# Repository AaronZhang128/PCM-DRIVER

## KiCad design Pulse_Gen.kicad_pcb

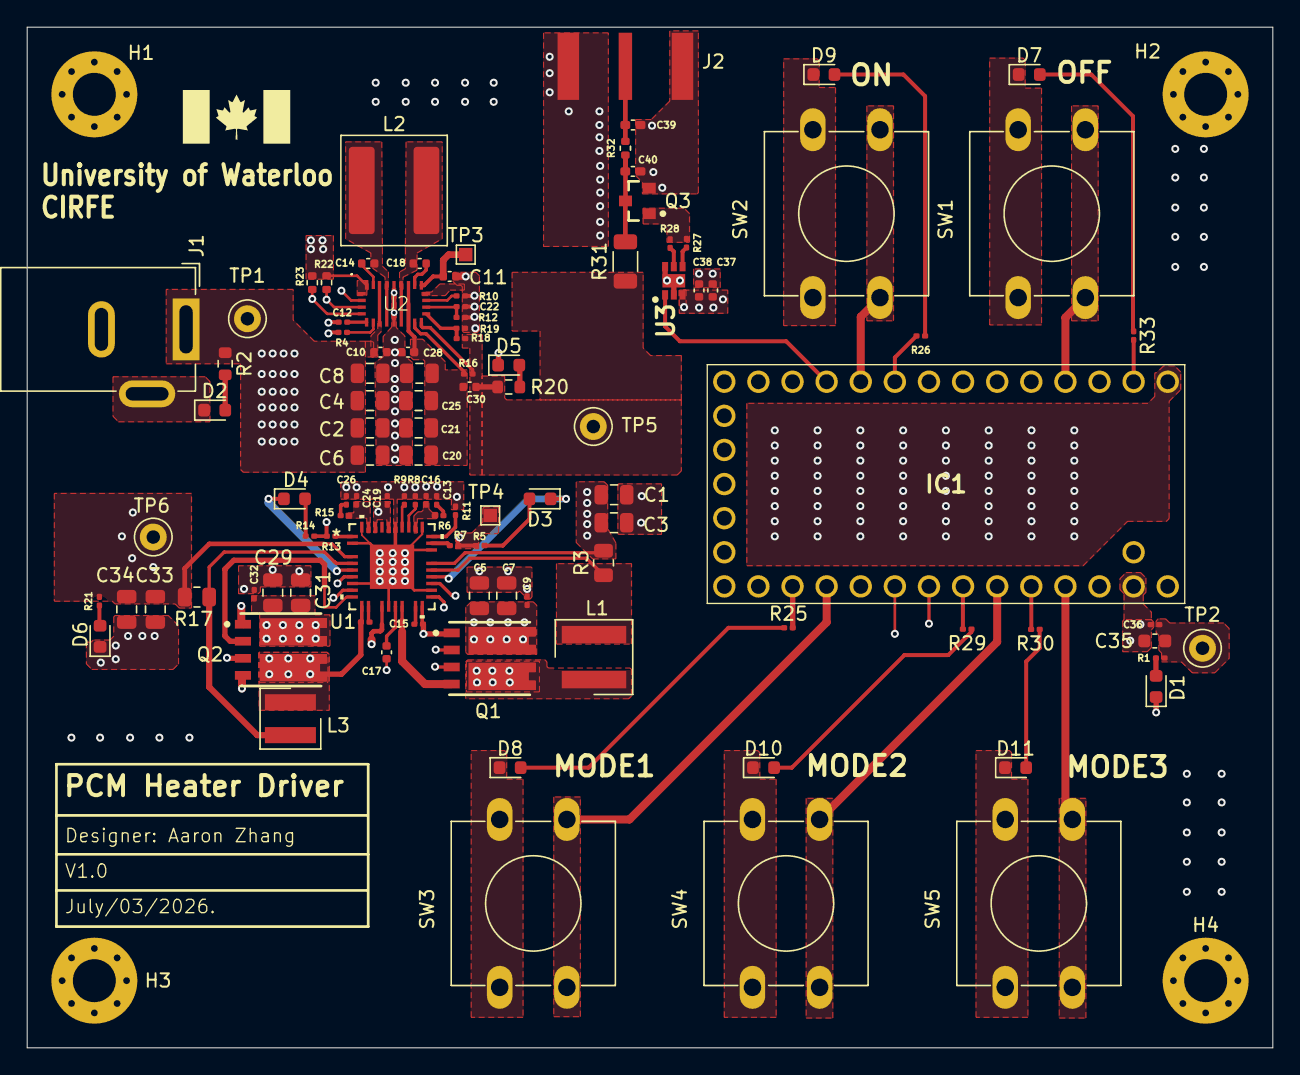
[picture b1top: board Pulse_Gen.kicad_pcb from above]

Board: 4 copper layers, 92.8 x 76.0 mm, 110 parts (0 on the bottom side), 68 nets.

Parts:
C1, C2, C3, C4, C5, C6, C7, C8, C20, C21, C25, C27, C29, C31, C33, C34: 22uF; C_0805_2012Metric
C9, C32: 10nF; C_0201_0603Metric
C10, C14, C18, C28, C30, C37: 0.1uF; C_0402_1005Metric
C11, C17: 4.7uF; C_0402_1005Metric
C12: 0.01uF; C_0201_0603Metric
C13: 4.7nF; C_0201_0603Metric
C15, C23, C36: 0.1uF; C_0201_0603Metric
C16: 82pF; C_0201_0603Metric
C19: 1uF; C_0201_0603Metric
C22: 12nF; C_0201_0603Metric
C24: 120pF; C_0201_0603Metric
C26: 8.2nF; C_0201_0603Metric
C35: 10uF; C_0603_1608Metric
C38: 1uF; C_0402_1005Metric
C39, C40: DNI; C_0402_1005Metric_Pad0.74x0.62mm_HandSolder
D1, D9: LED_G; LED_0603_1608Metric
D2, D8: LED_Y; LED_0603_1608Metric
D3, D4, D5, D7, D10: LED_R; LED_0603_1608Metric
D6, D11: LED_B; LED_0603_1608Metric
H1, H2, H3, H4: MountingHole_Pad; MountingHole_3.2mm_M3_Pad_Via
IC1: TEENSY_4.0; TEENSY40
J1: Barrel_Jack_Switch; BarrelJack_GCT_DCJ200-10-A_Horizontal
J2: 2081880-1; TE_2081880-1
L1: 4.7uH; L_Wurth_WE-XHMI-5030
L2: 4.7uH; L_Coilcraft_XAL7070-XXX
L3: 3.3uH; L_Wurth_WE-XHMI-4040
Q1, Q2: IPG20N04S4L-08A; INF-PG-TDSON-8-10
Q3: IRLML0040; SOT95P237X112-3N-2-V
R1, R5, R14, R29, R33: 604R; R_0201_0603Metric
R2, R20: 4k53; R_0603_1608Metric
R3: 8mR; R_0805_2012Metric
R4: 49K9; R_0201_0603Metric
R6: 8.45K; R_0201_0603Metric
R7: 24K9; R_0201_0603Metric
R8: 20K; R_0201_0603Metric
R9: 52.3K; R_0201_0603Metric
R10: DNI; R_0201_0603Metric
R11: 10K; R_0201_0603Metric
R12: 18k; R_0201_0603Metric
R13: 7.5K; R_0201_0603Metric
R15: 6.04K; R_0201_0603Metric
R16: 10m; R_0201_0603Metric
R17: 9mR; R_0805_2012Metric
R18: 100k; R_0201_0603Metric
R19: 5k76; R_0201_0603Metric
R21: 300R; R_0201_0603Metric
R22, R23: 4.7K; R_0402_1005Metric
R25: 510R; R_0201_0603Metric
R26: 570R; R_0201_0603Metric
R27, R28: 2R; R_0201_0603Metric
R30: 340R; R_0201_0603Metric
R31: 50R; R_1206_3216Metric
R32: 0R; R_0402_1005Metric
SW1, SW2, SW3, SW4, SW5: SW_Push; SW_PUSH-12mm
TP1: 24VIN; TestPoint_Keystone_5000-5004_Miniature
TP2, TP5, TP6: TestPoint; TestPoint_Keystone_5000-5004_Miniature
TP3, TP4: TestPoint; TestPoint_Pad_1.0x1.0mm
U1: VQFN36_6P1X6P1_TEX
U2: TPS55287_CORRECT
U3: SON65P200X200X80-7N

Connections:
+3.3V: C33.1, C34.1, R17.2, R21.1, R22.2, R23.2, TP6.1 (1_1), U1.3 (VOUT2), U2.1 (EN/UVLO), U2.21 (EXTVCC)
+5V: C1.1, C3.1, C35.1, C36.1, C37.2, C38.2, IC1.33 (VIN_(3.6_TO_5.5_VOLTS)), R1.1, R3.2, TP2.1 (1_1), U1.23 (BIAS1/VOUT1), U3.3 (VDD)
/FET/IRLML_G: Q3.1 (GATE), R27.1, R28.1
/FET/OUTH: R27.2, U3.4 (OUTH)
/FET/OUTL: R28.2, U3.5 (OUTL)
/MCU/D7: D8.2 (A), R25.1
/MCU/D8: D10.2 (A), R29.1
/MCU/D9: D11.2 (A), R30.1
/MCU/D10: D7.2 (A), R33.1
/MCU/D11: D9.2 (A), R26.1
/MCU/MCU_PIN0: IC1.2 (0), R33.2
/MCU/MCU_PIN2: IC1.4 (2), SW1.2
/MCU/MCU_PIN7: IC1.9 (7), R26.2
/MCU/MCU_PIN8: IC1.10 (8), SW2.2
/MCU/MCU_PIN15: IC1.22 (15), R25.2
/MCU/MCU_PIN16: IC1.23 (16), SW3.2
/MCU/MCU_PIN20: IC1.27 (20), R29.2
/MCU/MCU_PIN21: IC1.28 (21), SW4.2
/MCU/MCU_PIN22: IC1.29 (22), R30.2
/MCU/MCU_PIN23: IC1.30 (23), SW5.2
/POWER/24VIN: C2.1, C4.1, C5.1, C6.1, C7.1, C8.1, C9.2, C10.1, C29.1, C31.1, C32.2, J1.1, Q1.7 (DRAIN1), Q1.8 (DRAIN1), Q2.7 (DRAIN1), Q2.8 (DRAIN1), R2.1, TP1.1 (1_1), U1.8 (VIN), U2.7 (VIN)
/POWER/HO1: Q1.2 (GATE1), U1.18 (HO1)
/POWER/HO2: Q2.2 (GATE1), U1.9 (HO2)
/POWER/ISNS1+: L1.2, R3.1, U1.22 (ISNS1+)
/POWER/ISNS2+: L3.2, R17.1, U1.4 (ISNS2+)
/POWER/LM_CBOOT1: C15.1, U1.16 (CBOOT1)
/POWER/LM_CBOOT2: C23.1, U1.11 (CBOOT2)
/POWER/LM_CNFG: R11.1, U1.26 (CNFG)
/POWER/LM_COMP1: C16.1, R6.1, U1.28 (COMP1)
/POWER/LM_COMP2: C24.1, R15.1, U1.35 (COMP2)
/POWER/LM_FB1: R7.2, U1.25 (FB1)
/POWER/LM_FB2: R13.2, U1.1 (FB2)
/POWER/LM_PG1: D3.1 (K), U1.21 (PG1)
/POWER/LM_PG2: D4.1 (K), U1.5 (PG2)
/POWER/LM_RSS: R8.1, U1.29 (RSS)
/POWER/LM_RT: R9.1, U1.30 (RT)
/POWER/LM_VCC: C17.1, U1.14 (VCC)
/POWER/LM_VDDA: C19.1, R5.1, R7.1, R13.1, R14.1, TP4.1 (1_1), U1.6 (EN2), U1.20 (EN1), U1.32 (VDDA), U1.34 (PFM/SYNC)
/POWER/LO1: Q1.4 (GATE2), U1.15 (LO1)
/POWER/LO2: Q2.4 (GATE2), U1.12 (LO2)
/POWER/SW1: C15.2, L1.1, Q1.1 (SOURCE1), Q1.5 (DRAIN2), Q1.6 (DRAIN2), U1.17 (SW1)
/POWER/SW2: C23.2, L3.1, Q2.1 (SOURCE1), Q2.5 (DRAIN2), Q2.6 (DRAIN2), U1.10 (SW2)
/POWER/TP_BOOT1: C14.2, U2.20 (BOOT1)
/POWER/TP_BOOT2: C18.2, U2.19 (BOOT2)
/POWER/TP_CDC: R10.2, U2.16 (CDC)
/POWER/TP_COMP: C22.2, R12.2, U2.15 (COMP)
/POWER/TP_DITH: C12.1, U2.5 (DITH/SYNC)
/POWER/TP_FB: R18.2, R19.1, U2.14 (FB/INT)
/POWER/TP_FSW: R4.2, U2.6 (FSW)
/POWER/TP_SW1: C14.1, L2.1, U2.8 (SW1)
/POWER/TP_SW2: C18.1, L2.2, U2.10 (SW2)
/POWER/TP_VCC: C11.2, TP3.1 (1_1), U2.18 (VCC)
/POWER/VOUT: C20.1, C21.1, C25.1, C27.1, C28.1, C30.1, R16.1, U2.11 (VOUT), U2.12 (ISP)
CTRD_VOUT: C30.2, R16.2, R18.1, R20.1, R31.2, TP5.1 (1_1), U2.13 (ISN)
GATE_DRIVER: IC1.11 (9), U3.1 (IN+)
GNDREF: C1.2, C2.2, C3.2, C4.2, C5.2, C6.2, C7.2, C8.2, C9.1, C10.2, C11.1, C12.2, C13.2, C16.2, C17.2, C19.2, C20.2, C21.2, C22.1, C24.2, C25.2, C26.2, C27.2, C28.2, C29.2, C31.2, C32.1, C33.2, C34.2, C35.2, C36.2, C37.1, C38.1, C39.1, C40.1, D1.1 (K), D2.1 (K), D5.1 (K), D6.1 (K), D7.1 (K), D8.1 (K), D9.1 (K), D10.1 (K), D11.1 (K), H1.1 (1_1), H2.1 (1_1), H3.1 (1_1), H4.1 (1_1), IC1.1 (GND_1), IC1.17 (GND_2), IC1.32 (GND_3), J1.2, J1.3, J2.2, J2.3, J2.4, J2.5, Q1.3 (SOURCE2), Q2.3 (SOURCE2), Q3.2 (SOURCE), R4.1, R8.2, R9.2, R10.1, R11.2, R12.1, R19.2, SW1.1, SW2.1, SW3.1, SW4.1, SW5.1, U1.2 (GND), U1.7 (GND), U1.13 (PGND), U1.19 (GND), U1.24 (GND), U1.27 (GND), U1.31 (AGND), U1.36 (GND), U1.37 (EPAD), U2.2 (MODE), U2.9 (PGND), U2.17 (AGND), U3.2 (GND), U3.6 (IN-), U3.7 (EP)
unnamed: C13.1, R6.2
unnamed: C26.1, R15.2
unnamed: C39.2, J2.1, R32.1
unnamed: D1.2 (A), R1.2
unnamed: D2.2 (A), R2.2
unnamed: D3.2 (A), R5.2
unnamed: D4.2 (A), R14.2
unnamed: D5.2 (A), R20.2
unnamed: D6.2 (A), R21.2
unnamed: C40.2, Q3.3 (DRAIN), R31.1, R32.2
TP_SCL: IC1.26 (19), R23.1, U2.3 (SCL)
TP_SDA: IC1.25 (18), R22.1, U2.4 (SDA)

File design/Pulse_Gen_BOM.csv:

"Reference","Qty","Value","DNP","Exclude from BOM","Exclude from Board","Datasheet","Footprint","MPN"
"C1,C2,C3,C4,C5,C6,C7,C8,C20,C21,C25,C27,C29,C31,C33,C34","16","22uF","","","","","Capacitor_SMD:C_0805_2012Metric","C3216X5R1V226M160AC"
"C9,C32","2","10nF","","","","","Capacitor_SMD:C_0201_0603Metric","UMK063BJ103KP-F"
"C10,C15,C18,C28,C30,C37","6","0.1uF","","","","","Capacitor_SMD:C_0402_1005Metric","CL05B104KO5NNNC,CL05B104KP5NNNC,GCM155R71H104KE02J"
"C11,C14","2","4.7uF","","","","","Capacitor_SMD:C_0402_1005Metric","CL05A475MP5NRNC"
"C12","1","0.01uF","","","","","Capacitor_SMD:C_0201_0603Metric","GRM033R71A103KA01D"
"C13","1","4.7nF","","","","","Capacitor_SMD:C_0201_0603Metric","GRM033R70J472KA01D"
"C16,C23,C36","3","0.1uF","","","","","Capacitor_SMD:C_0201_0603Metric","CL03A104KP3NNNC"
"C17","1","82pF","","","","","Capacitor_SMD:C_0201_0603Metric","0201ZA820JAT2A"
"C19","1","1uF","","","","","Capacitor_SMD:C_0201_0603Metric","CL03A105MP3NSNC"
"C22","1","12nF","","","","","Capacitor_SMD:C_0201_0603Metric","GRM033R61A123ME84D"
"C24","1","120pF","","","","","Capacitor_SMD:C_0201_0603Metric","GRM0335C1E560FA01D"
"C26","1","8.2nF","","","","","Capacitor_SMD:C_0201_0603Metric","GRM033R71A392KA01D"
"C35","1","10uF","","","","","Capacitor_SMD:C_0603_1608Metric","GRM188C81A106MA73D"
"C38","1","1uF","","","","","Capacitor_SMD:C_0402_1005Metric","GRM155Z71A105KE01J"
"D1,D9","2","LED_G","","","","","LED_SMD:LED_0603_1608Metric","LTST-C190KGKT"
"D2,D8","2","LED_Y","","","","","LED_SMD:LED_0603_1608Metric","LTST-C190KSKT"
"D3,D4,D5,D7,D10","5","LED_R","","","","","LED_SMD:LED_0603_1608Metric","LTST-C191KRKT"
"D6,D11","2","LED_B","","","","","LED_SMD:LED_0603_1608Metric","LTST-C190TBKT"
"J1","1","Barrel_Jack_Switch","","","","","Connector_BarrelJack:BarrelJack_GCT_DCJ200-10-A_Horizontal","RAPC712BKZ"
"J2,J4","2","Conn_01x14_Socket","","","","","Connector_PinSocket_2.54mm:PinSocket_1x14_P2.54mm_Vertical","PPTC141LFBN-RC"
"J3","1","Conn_01x05_Pin","","","","","Connector_PinSocket_2.54mm:PinSocket_1x05_P2.54mm_Vertical","PPTC051LFBN-RC"
"J5","1","2081880-1","","","","","SMA:TE_2081880-1","17-2081880-1-ND"
"L1","1","4.7uH","","","","","4.7uH:L_Wurth_WE-XHMI-5030","7443845030047"
"L2","1","4.7uH","","","","","Inductor_SMD:L_Coilcraft_XAL7070-XXX","XAL7070-472MEC"
"L3","1","3.3uH","","","","","3.3uH:L_Wurth_WE-XHMI-4040","74439325033"
"Q1,Q2","2","IPG20N04S4L-08A","","","","","IPG20N04S4L-08Atest:INF-PG-TDSON-8-10","IPG20N04S4L-08A"
"Q3","1","IRLML0040","","","","","IRLML0040TRPBF:SOT95P237X112-3N-2-V","IRLML0040TRPBF"
"R1,R5,R14,R24,R27","5","604R","","","","","Resistor_SMD:R_0201_0603Metric","CRCW0201604RFKED"
"R2,R20","2","4k53","","","","","Resistor_SMD:R_0603_1608Metric","ERJ-UP3F4531V"
"R3","1","8mR","","","","","Resistor_SMD:R_0805_2012Metric","ERJ-6LWFR008V"
"R4","1","49K9","","","","","Resistor_SMD:R_0201_0603Metric","ERJ-1GNF4992C"
"R6","1","8.45K","","","","","Resistor_SMD:R_0201_0603Metric","RC0201FR-078K45L"
"R7","1","24K9","","","","","Resistor_SMD:R_0201_0603Metric","ERJ-1GNF2492C"
"R8","1","20K","","","","","Resistor_SMD:R_0201_0603Metric","TNPW020120K0BEED"
"R9","1","52.3K","","","","","Resistor_SMD:R_0201_0603Metric","ERJ-1GNF5232C"
"R10","1","DNI","DNP","","","","Resistor_SMD:R_0201_0603Metric",""
"R11","1","10K","","","","","Resistor_SMD:R_0201_0603Metric","RC0201FR-0710KL"
"R12","1","18k","","","","","Resistor_SMD:R_0201_0603Metric","RC0201FR-0718KL"
"R13","1","7.5K","","","","","Resistor_SMD:R_0201_0603Metric","ERJ-1GNF7501C"
"R15","1","6.04K","","","","","Resistor_SMD:R_0201_0603Metric","RC0201FR-0712K1L"
"R16","1","10m","","","","","Resistor_SMD:R_0201_0603Metric","CSS0201FT10L0"
"R17","1","9mR","","","","","Resistor_SMD:R_0805_2012Metric","CRF0805-FZ-R009ELF"
"R18","1","100k","","","","","Resistor_SMD:R_0201_0603Metric","RC0201FR-07100KL"
"R19","1","5k76","","","","","Resistor_SMD:R_0201_0603Metric","ERJ-1GNF5761C"
"R21","1","300R","","","","","Resistor_SMD:R_0201_0603Metric","RC0201JR-07300RL"
"R22,R23","2","4.7K","","","","","Resistor_SMD:R_0402_1005Metric","CRCW04024K70FKED"
"R25","1","510R","","","","","Resistor_SMD:R_0201_0603Metric","RC0201JR-07510RL"
"R26","1","570R","","","","","Resistor_SMD:R_0201_0603Metric","ERJ-1GNF5760C"
"R28","1","340R","","","","","Resistor_SMD:R_0201_0603Metric","ERJ-1GNF3400C"
"R29,R30","2","2R","","","","","Resistor_SMD:R_0201_0603Metric","ERJ-1GNJ2R0C"
"R31","1","50R","","","","TVC1206CT-50R0JN-2STR","Resistor_SMD:R_1206_3216Metric","TVC1206CT-50R0JN-2STR"
"R32","1","0R","","","","","Resistor_SMD:R_0402_1005Metric","ERJ-2GE0R00X"
"SW1,SW2,SW3,SW4,SW5","5","SW_Push","","","","","Button_Switch_THT:SW_PUSH-12mm","1568-10302-ND"
"TP1","1","24VIN","","","","","TestPoint:TestPoint_Keystone_5000-5004_Miniature",""
"TP2,TP5,TP6","3","TestPoint","","","","","TestPoint:TestPoint_Keystone_5000-5004_Miniature",""
"TP3,TP4","2","TestPoint","","","","","TestPoint:TestPoint_Pad_1.0x1.0mm",""
"U1","1","","","","","","LM5137:VQFN36_6P1X6P1_TEX","LM5137"
"U2","1","","","","","","TPS55287:TPS55287_CORRECT","TPS55287"
"U3","1","","","","","","LMG1025-Q1:SON65P200X200X80-7N","LMG1025QDEETQ1"
